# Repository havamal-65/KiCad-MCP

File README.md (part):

# KiCad MCP Server

A pure Python [Model Context Protocol (MCP)](https://modelcontextprotocol.io) server for KiCad EDA automation. Enable AI assistants like Claude, Cursor, and others to interact with KiCad projects programmatically.

## Overview

KiCad MCP Server provides a standardized interface for AI assistants to read, analyze, and modify KiCad electronic design automation (EDA) files. It supports multiple backend implementations to work with KiCad in different environments and use cases.

### Key Features

- **121 MCP Tools** across 11 categories:
  - 📋 **Project Management** (15 tools): Create projects, open projects, list files, read/write metadata, text variable management, query backend info, query active KiCad project (IPC-first, with bridge fallback), PCB workflow reference, plan capture and retrieval, **KiCad 9→10 project format upgrade** (kicad-cli-driven, backed up, one-way), **8-item startup gate checklist**
  - 📐 **Schematic Operations** (29 tools): Create schematics from scratch, place/remove/move components, wire routing, labels (add/remove/edit label text), no-connects, junctions, power symbols, bulk component / power-symbol / pin-net / no-connect / move operations (drop ~200 calls per design to ~10), property editing, **symbol attribute authoring and editing** (`in_bom` / `on_board` / `dnp` / `exclude_from_sim`), pin position queries (with `extends` resolution **and audited rotation/mirror math against eeschema**), net connectivity analysis, hierarchical sheet traversal, schematic-to-PCB comparison and sync (with **PlacementIntent** schematic-driven anchoring + sheet-path propagation)
  - 🔌 **PCB Board Operations** (21 tools): Read boards, place/move components, add tracks/vias/board outlines, assign nets, query design rules, **author/list/delete copper pour zones** plus refill, **silkscreen refdes tidying** (relocate-first, hide-fallback), query layer stackup, write IPC-2221/JLCPCB design rules, geometry-driven auto-placement (with **sheet-hierarchy clustering** and **anchors** parameter so place_at_edge work survives bulk placement), **board-size verification gate**, full schematic-to-routed-PCB pipeline (with mandatory pre-flight gate), **diff two board snapshots**, **anchor an edge-facing connector at a named board edge with correct outward rotation**
  - 📚 **Library Search** (8 tools): Search symbols/footprints, list libraries, get symbol/footprint info, suggest footprints for a symbol (with physical dimensions), query footprint courtyard dimensions, **estimate board size from footprint list**
  - 📦 **Library Management** (9 tools): Clone repos, register sources, import symbols/footprints, create project libraries
  - ✅ **Design Rule Checks** (13 tools): Run DRC and ERC validations, file-based schematic and board validation (no kicad-cli), kicad-cli strict schematic validation, query board design rules, **symbol/footprint pad-match validator**, **pre-sync schematic completeness check**, **fast courtyard overlap check**, **placement-quality gate** (keep-out intrusion + net-aware metric), **detect edge-facing connectors** (USB-C, JST, audio jacks, etc.), **validate connector orientations** with autoroute hash-gate that refuses to route over inward-facing connectors
  - 📤 **Export Operations** (9 tools): Export Gerbers, drill files, BOMs, pick-and-place, PDFs (with actionable error diagnostics), **3D STEP and VRML models** (STEP with a three-way success / partial / error verdict), **verify 3D model references resolve on disk**, **render a board or schematic to an image for visual self-inspection**
  - 🏭 **Manufacturing** (1 tool): One-call **manufacturing-readiness audit** — DRC + board-size + courtyard + 3D-model + all five fab artifacts with a structured ship/no-ship verdict
  - 🎛️ **Design Variants** (4 tools, KiCad 10+): Create/delete variants, set per-component overrides (DNP, BOM/position exclusion, field values — schematic and board sides in one call), list variants with cross-file consistency checks; all writes kicad-cli-validated and atomic, structured refusal on KiCad 9
  - 🔀 **Auto-Routing** (6 tools): PCB trace auto-routing — **TraceMaker preferred when its WSL runtime is detected, with automatic FreeRouting fallback** (both optional; `router` parameter forces either engine), **clean board for routing**, **clear all routes for re-placement**
  - 🔍 **Parts Catalog** (6 tools): Index and search third-party KiCad library sources by MPN, install parts into project libraries

- **Plugin Backend Architecture**: `PluginDirectBackend` routes each operation to the right subsystem — no fallback ambiguity:
  - **Board read/write** → KiCad IPC API (`kicad-python`/`kipy`) as the primary live path, TCP bridge to embedded `pcbnew` as fallback, then the file backend when KiCad is closed (writes safe-refuse rather than clobber a live board). Requires KiCad open for live ops.
  - **Schematic read/write** → Pure Python file backend (no KiCad instance required)
  - **DRC / export** → `kicad-cli` subprocess
  - **Library search/management** → Pure Python file backend
- **Safe Response Sizes**: Large list results (symbols, wires, tracks, components) are automatically capped to prevent AI token-limit errors. Truncated fields include `<field>_total` and `<field>_truncated` metadata so you always know the full count.
- **Change Tracking**: Built-in logging of all operations for debugging and auditing
- **Backup Support**: Automatic file backups before modifications
- **Flexible Configuration**: Environment variables, CLI args, or programmatic config

## Installation

### Requirements

- Python 3.10 or higher
- KiCad 7.0+ (optional, depending on backend)

### From PyPI (Coming Soon)

```bash
python -m venv .venv
source .venv/bin/activate   # Windows: .venv\Scripts\activate
pip install kicad-mcp
```

### From Source

```bash
git clone https://github.com/havamal-65/KiCad-MCP.git
cd KiCad-MCP
pip install -e .
```

### Optional Dependencies

Activate the venv first, then install the extras inside it:

```bash
source .venv/bin/activate   # Windows: .venv\Scripts\activate
```

For auto-routing functionality, install at least one routing engine (the `autoroute`
tool prefers TraceMaker when it is available and falls back to FreeRouting
automatically — see [Auto-Routing](#auto-routing-6-tools---optional)):

- **TraceMaker** (Windows, via WSL2): build [TraceMaker](https://github.com/DingoOz/TraceMaker)
  inside a WSL2 distro. By default the tool looks for distro `tracemaker-build` and
  binary `~/TraceMaker/build/cpu-only/src/app/tracemaker`; override with
  `KICAD_MCP_TRACEMAKER_DISTRO` and `KICAD_MCP_TRACEMAKER_BIN`. Set
  `KICAD_MCP_NO_TRACEMAKER=1` to disable detection entirely.
- **FreeRouting** (all platforms, requires Java):
  - Download [FreeRouting JAR](https://github.com/freerouting/freerouting/releases)
  - Ensure Java Runtime Environment (JRE) is installed
  - Set `KICAD_MCP_FREEROUTING_JAR` and `KICAD_MCP_JAVA_PATH` environment variables (or let the tool auto-detect)

For development:
```bash
pip install kicad-mcp[dev]
```

For the desktop launcher (a status dashboard that brings up the whole stack — see
[Desktop Launcher](#desktop-launcher-ui) below):
```bash
pip install kicad-mcp[launcher]   # pywebview + psutil
```
On Windows the launcher uses the system **WebView2** runtime (preinstalled on
Windows 11). It is a standalone dev tool run from source and is **not** part of the
MCP server install.

## Claude Code Skill: `/build-pcb`

When using this server with Claude Code, invoke `/build-pcb [project description]` to
start a **professional, phased PCB design session**. The skill mirrors IPC/JEDEC
industry practice with seven gated phases and a report + user confirmation between each:

| Phase | Name | Gate condition |
|-------|------|---------------|
| 1 | Environment & Requirements | `get_startup_checklist.ready_for_pcb` |
| 2 | Schematic Capture | All components placed, ≥1 net |
| 3 | Schematic Verification | `validate_schematic_for_pcb.ready_for_pcb_sync`, ERC clean |
| 4a | Sync & Survey | every ref from `identify_edge_facing_connectors` has a planned edge |
| 4b | Anchor Connectors | `validate_connector_orientations.passed` after `place_at_edge` for each |
| 4c | Bulk Placement | every non-anchored ref placed; anchors passed via `auto_place(anchors=[...])` |
| 4d | Overlap Check | `check_courtyard_overlaps.passed` |
| 4e | Final Orientation Re-check | `validate_connector_orientations.passed` (autoroute refuses if not) |
| 5 | Routing | Zero unrouted connections |
| 6 | Design Verification | `run_drc.passed` |
| 7 | Manufacturing Outputs | All six export files generated |

After each phase Claude prints a `## Phase N Report` block and pauses for your
confirmation before continuing. Hard gates prevent routing over courtyard overlaps,
routing past inward-facing connectors, or syncing a schematic with blocking issues.

---

## Quick Start

### Plugin Entry Point (recommended on Windows with KiCad 9)

The plugin entry point routes board operations through the in-KiCad TCP bridge (`kicad_mcp_bridge`) and is the primary supported path for live PCB work.

**Prerequisites**: Install the bridge plugin and restart KiCad (see [Plugin Backend Setup](#plugin-backend-setup) below).

```bash
python -m kicad_mcp_plugin
```

### Run the Server

#### Stdio Transport (for Claude Desktop, Cursor, etc.)

```bash
python -m kicad_mcp_plugin
```

#### SSE Transport (for web clients)

```bash
python -m kicad_mcp_plugin --transport sse --sse-host 127.0.0.1 --sse-port 8765
```

## Desktop Launcher (UI)

A standalone desktop app that brings up and monitors the whole KiCad ↔ MCP stack
from one window — so you don't have to start pcbnew, the MCP server, and Claude Code
by hand. It's a **status-first dashboard** that shows, live, whether an AI agent can
currently reach and edit a board.

**What it shows** (all real, polled from the same health collectors the MCP uses —
no mock data):

- **pcbnew bridge** and **MCP server** status tiles (connected / running / pid / uptime)
- the **`ready_for_pcb` gate** — a live `n/6` progress bar over the six startup checks
- the four **backends** (`plugin`, `file`, `cli`, `subprocess`) and their availability
- **tool-activity** and **server.log** feeds (only real events — quiet when idle)
- an **actionable guidance** callout that turns a passive status into the next step
  (server stopped → *Start everything*; bridge down → *Open PCB editor*; checks
  incomplete → *Reload board*)

**Actions**: a project picker plus **Start everything** (opens pcbnew on the selected
board, starts the MCP HTTP server, and launches a Claude Code session), **Restart MCP**
(reloads server code without the manual kill + `/mcp`), and **Stop MCP**.

**Run it** (after `pip install kicad-mcp[launcher]`):

```bash
python -m launcher
```

On Windows you can also double-click / run `launcher/launcher.ps1` for a windowless
(`pythonw`) launch. The launcher never modifies the MCP server or the bridge; it
reuses `scripts/mcp_health_monitor.py`'s collectors for status and drives the same
tools you'd call by hand. Configure it with the same environment variables as the
server (e.g. `KICAD_MCP_HTTP_HOST`/`KICAD_MCP_HTTP_PORT`, `KICAD_MCP_PROJECTS_ROOT`).

### Packaged app (no Python required)

A double-click Windows installer bundles the launcher, the MCP server, and a
Python runtime — nothing to `pip install`, no terminal:

1. Build (or download) `KiCad-MCP-Launcher-Setup-<version>.exe` — built from a
   checkout with one command: `pwsh -File installer\build.ps1`.
2. Run it. **The installer is unsigned**, so Windows SmartScreen will warn:
   click **More info → Run anyway**. (Unsigned-with-docs is the deliberate
   ship decision; the build script signs everything automatically if you
   supply a code-signing certificate: `installer\build.ps1 -CertPath ...`.)
3. It installs per-user (no admin prompt) to
   `%LOCALAPPDATA%\Programs\KiCad-MCP Launcher`, adds a Start-Menu shortcut,
   and opens the launcher. On first run the **Setup view** walks the
   remaining pieces: detect KiCad, install the bridge, register the MCP with
   Claude Code — all from the window.
4. KiCad itself stays a prerequisite (the wizard links to its download);
   uninstalling removes the app but deliberately leaves the bridge and your
   MCP client config in place (they belong to your KiCad/client setup).

The `pip install` dev path above keeps working unchanged; the packaged app is
additive. Requires the Microsoft WebView2 runtime (preinstalled on Windows 11;
the app shows the official download link if it's missing).

## Configuration

### Environment Variables

```bash
# Transport: stdio, sse, streamable-http
KICAD_MCP_TRANSPORT=stdio

# Logging level: DEBUG, INFO, WARNING, ERROR
KICAD_MCP_LOG_LEVEL=INFO

# Log file path (default: ~/.kicad-mcp/logs/server.log)
KICAD_MCP_LOG_FILE=

# Explicit path to kicad-cli executable
KICAD_MCP_KICAD_CLI_PATH=

# Enable file backups before modification (default: true)
KICAD_MCP_BACKUP_ENABLED=true

# Bridge port (default: 9760)
KICAD_MCP_PLUGIN_PORT=9760

# Network bind (only used with --transport sse / streamable-http)
KICAD_MCP_SSE_HOST=127.0.0.1
KICAD_MCP_SSE_PORT=8765
```

### Programmatic Configuration

```python
from kicad_mcp_plugin.config import KiCadPluginConfig
from kicad_mcp_plugin.server import create_plugin_server

config = KiCadPluginConfig(log_level="INFO")
mcp = create_plugin_server(config)
mcp.run(transport="stdio")
```

## Client Integration

The repo ships bootstrap scripts for the plugin entry point:

- **`run_plugin.ps1`** — Windows (PowerShell 7+)
- **`run_plugin.sh`** — macOS / Linux

These automatically create a virtual environment and install all dependencies on first run, and they clear inherited `PYTHONHOME` / `PYTHONPATH` overrides so MCP clients use the repo's venv instead of global Python packages.

### Codex CLI

Register the server once with `codex mcp add`:

Windows:

```powershell
codex mcp add kicad `
  --env KICAD_MCP_LOG_LEVEL=INFO `
  -- "C:\Windows\System32\WindowsPowerShell\v1.0\powershell.exe" `
  -ExecutionPolicy Bypass `
  -NonInteractive `
  -File "C:\path\to\KiCad-MCP\run_plugin.ps1"
```

macOS / Linux:

```bash
codex mcp add kicad \
  --env KICAD_MCP_LOG_LEVEL=INFO \
  -- /path/to/KiCad-MCP/run_plugin.sh
```

Verify with:

```bash
codex mcp get kicad
```

### Claude Code (recommended)

A `.mcp.json` is included at the repo root. Claude Code picks it up automatically when you open the folder, so no manual config is required. It uses the plugin entry point (`kicad_mcp_plugin`) by default, which requires KiCad to be open with the bridge installed.

### Claude Desktop — Windows

Add to `%APPDATA%\Claude\claude_desktop_config.json`:
Use an absolute PowerShell path to avoid `Executable not found in $PATH: "powershell"` startup errors.

```json
{
  "mcpServers": {
    "kicad": {
      "command": "C:\\Windows\\System32\\WindowsPowerShell\\v1.0\\powershell.exe",
      "args": [
        "-ExecutionPolicy", "Bypass",
        "-NonInteractive",
        "-File", "C:\\path\\to\\KiCad-MCP\\run_plugin.ps1"
      ],
      "env": {
        "KICAD_MCP_LOG_LEVEL": "INFO"
      }
    }
  }
}
```

### Claude Desktop — macOS / Linux

Add to `~/Library/Application Support/Claude/claude_desktop_config.json` (macOS) or `~/.config/Claude/claude_desktop_config.json` (Linux):

```json
{
  "mcpServers": {
    "kicad": {
      "command": "/path/to/KiCad-MCP/run_plugin.sh",
      "env": {
        "KICAD_MCP_LOG_LEVEL": "INFO"
      }
    }
  }
}
```

### Cursor

Add to your Cursor MCP settings (use `run_plugin.ps1` on Windows, `run_plugin.sh` on macOS/Linux as above).

### Manual setup (advanced)

If you prefer to manage your own venv:

```bash
python -m venv .venv
source .venv/bin/activate   # Windows: .venv\Scripts\activate
pip install -e .
python -m kicad_mcp_plugin
```

## Available Tools

### Project Management (15 tools)
- `open_kicad`: Launch KiCad and wait for the bridge to become ready
- `open_project`: Open a KiCad project and return its structure
- `list_project_files`: List all KiCad-related files in a project directory
- `get_project_metadata`: Read detailed metadata from a KiCad project file
- `save_project`: Trigger save for an open KiCad project (requires bridge)
- `get_backend_info`: Get information about available backends and their capabilities
- `get_active_project`: Query the currently open KiCad project and board path (requires bridge)
- `get_text_variables`: Get all project-level text variables (`${VAR}` substitutions)
- `set_text_variables`: Set one or more project-level text variables
- `create_project`: Create a new KiCad project with blank `.kicad_pro`, `.kicad_sch`, and `.kicad_pcb` files
- `get_pcb_workflow`: Return a structured 11-step PCB design workflow reference (JSON) showing the recommended tool sequence from project creation through DRC
- `plan_project`: Record a structured project plan into a `project_plan.json` file. When `board_width_mm`/`board_height_mm` are 0 (default) and footprint IDs are included in `key_components`, auto-estimates board dimensions from courtyard bounds. Emits a `size_warning` when provided dimensions are more than 15% smaller than the estimate.
- `read_project_plan`: Read back the saved project plan for a given project directory
- `upgrade_project_format`: Upgrade a project's schematic and board files from KiCad-9 to KiCad-10 format via KiCad's own `kicad-cli sch/pcb upgrade`, backing up every changed file first. One-way (KiCad 9 cannot re-open v10 files; the `.kicad_mcp_backups/` copies are the rollback); refuses without touching any file if no KiCad-10 kicad-cli is available. Needed before the Design Variants tools on a v9-format project
- `get_startup_checklist`: Run an eight-item PASS/WARN/FAIL gate before any board operation: KiCad running (counts pcbnew/eeschema too) · IPC API server reachable · bridge reachable · bridge version · PCB editor open (board-ready aware — distinguishes "still loading" from "no board") · live board ↔ file coherence (WARNs with a reload advisory when the open board's component set or Edge.Cuts outline diverges from the file on disk) · kicad-cli on PATH · active project loaded. A down bridge is a non-blocking WARN whenever the IPC path already serves the open board (and vice-versa). Returns `ready_for_pcb` bool and `required_actions` list. **Must be called at the start of every session involving PCB operations.**

### Schematic Operations (29 tools)
- `read_schematic`: Read complete schematic structure (symbols, wires, labels, no-connects, junctions). Every symbol row carries the four attribute flags (`in_bom`, `on_board`, `dnp`, `exclude_from_sim`)
- `create_schematic`: Create a new, empty KiCad 8+ schematic file with proper structure
- `add_component`: Place symbols with rotation, mirror, footprint, custom properties, KiCad 8+ instance data, and optional symbol attribute flags (`in_bom`, `on_board`, `dnp`, `exclude_from_sim` — e.g. keep a mounting hole out of the BOM at placement time)
- `add_components`: **Bulk** — place N components in one call (single file read/write). Prefer over looping `add_component`.
- `add_wire`: Draw wire connections between two points
- `add_label`: Add net labels (net, global, hierarchical)
- `remove_label`: Remove a net label by its position
- `set_label_text`: Change the text of an existing net label
- `add_no_connect`: Add no-connect (X) markers to unused pins
- `add_no_connects`: **Bulk** — mark N unused pins in one call.
- `add_power_symbol`: Add power symbols (+3V3, GND, VCC, etc.) with auto-incrementing references
- `add_power_symbols`: **Bulk** — place N power symbols in one call; #PWR refs auto-incremented across the batch.
- `connect_pins`: **Bulk** — net N pins together with one call by emitting stub-and-label connectivity. Replaces the `add_wire + add_label` × N pattern (~6 calls per net) with one call.
- `add_junction`: Add junction dots at wire intersections
- `remove_component`: Remove a placed component by reference designator
- `remove_wire`: Remove a wire segment by its endpoint coordinates
- `remove_no_connect`: Remove a no-connect marker by its position
- `move_schematic_component`: Move a component to a new position with optional rotation (shifts property labels too)
- `move_components`: **Bulk** — reposition N components in one call (single file read/write).
- `update_component_property`: Update or add a property (Value, Footprint, MPN, etc.) on a placed component
- `set_symbol_attributes`: Edit the four attribute flags (`in_bom`, `on_board`, `dnp`, `exclude_from_sim`) on an already-placed symbol — only the flags you pass change; multi-unit symbols are updated across every unit and the per-unit results reported
- `get_symbol_pin_positions`: Get absolute schematic coordinates for each pin of a placed symbol; resolves `extends` chains so symbols like ATtiny85-20S and AMS1117-3.3 work correctly, and applies KiCad's rotation/mirror transform (audited against eeschema's own placement so rotated/mirrored symbols resolve correctly)
- `get_pin_net`: Get the net name connected to a specific pin of a symbol
- `get_net_connections`: Get all connections (pins, labels, wires) on a named net
- `get_sheet_hierarchy`: Get the hierarchical sheet tree from a root schematic
- `compare_schematic_pcb`: Detect mismatches between schematic and PCB (missing components, footprint/value differences)
- `sync_schematic_to_pcb`: Synchronize schematic components to the PCB (auto-place missing, update values, sync pin nets to pad net assignments). Reads each symbol's `PlacementIntent` custom property: `edge:north|south|east|west` anchors the corresponding footprint at that edge with correct outward rotation (skipped with a warning if no Edge.Cuts outline yet); `cluster:NAME` attaches a `ClusterId` to the footprint so `auto_place` keeps that subsystem geometrically grouped. Sheet hierarchy from `.kicad_sch` is propagated to placed footprints as a `(path "/UUID/...")` clause so `auto_place` clusters by schematic block automatically.
- `annotate_schematic`: Auto-annotate component reference designators
- `generate_netlist`: Generate netlist from schematic

### PCB Board Operations (21 tools)
- `read_board`: Read complete board structure
- `get_board_info`: Get board metadata (title, revision, layers, counts)
- `place_component`: Place a component footprint on the board
- `move_component`: Move an existing component to a new position
- `place_at_edge`: Anchor an edge-facing connector at the named board edge (`north` / `south` / `east` / `west`) with the correct outward rotation and a configurable courtyard-clearance offset. Reads the connector's local-frame mating face (via the same detection `validate_connector_orientations` uses) and computes the rotation that makes it point outward. Use in `/build-pcb` Phase 4b before `auto_place(anchors=[...])`.
- `add_track`: Add a copper track segment
- `add_via`: Add a via (through-hole, blind, or buried)
- `add_board_outline`: Add or replace the Edge.Cuts board outline with a rectangle at the specified origin and size. When called via `pcb_pipeline`, the board is automatically centered at the KiCad canvas origin (0, 0) so it always appears in the middle of the work area.
- `assign_net`: Assign a net to a component pad
- `get_design_rules`: Get the board's design rules (clearances, track widths, via sizes)
- `refill_zones`: Refill all copper pour zones on a board
- `add_zone`: Add a copper pour zone (e.g. a GND plane) from an explicit polygon or, with `follow_board_outline`, a rectangle derived from the Edge.Cuts bounding box inset by a margin. The zone is filled via a kicad-cli subprocess so the saved file carries real fill geometry
- `list_zones`: List every zone on a board, including rule (keep-out) areas — reads the saved `.kicad_pcb` directly so the answer is always file truth
- `delete_zone`: Delete one copper zone by name or uuid (rule areas are refused — use the keep-out tools for those)
- `tidy_silkscreen`: Reduce silkscreen DRC warnings by tidying reference-designator text — relocate each clipped/overlapping refdes to the nearest clear spot first, hide only small passives with nowhere clear to go (IC and connector refs are never hidden), then re-run DRC and report the delta
- `get_stackup`: Get the layer stackup definition for a board
- `verify_board_size`: Gate that asserts the chosen board size accommodates the placed parts plus manufacturing tolerances (panelization keepout, mounting holes, fiducials, routing channels). Returns `{passed, total_required_mm2, available_mm2, shortfall_breakdown, suggested_min_dimensions}` and is a precondition on `auto_place`.
- `set_board_design_rules`: Write manufacturing-enforceable design rules into the `.kicad_pro` `net_settings.classes` Default entry. Preset `"class2"` applies IPC-2221 Class 2 / IPC-7351 Level B values (0.20 mm clearance, 0.25 mm trace, 0.30 mm via drill). Preset `"fab_jlcpcb"` applies JLCPCB 2-layer standard rules.
- `auto_place`: Geometry-driven bin-packing placement. Reads the courtyard extents for every footprint, sorts by component class (connectors → ICs → discretes → transistors → LEDs → others), and packs components into rows with a guaranteed courtyard-to-courtyard gap ≥ `clearance_mm`. Returns `utilization_pct` (courtyard area / board area) and warns when >70%. Accepts an optional `anchors=[ref,...]` list — those refs are skipped so `place_at_edge`'s work survives bulk placement. Groups components by schematic sheet path (or explicit `PlacementIntent: cluster:NAME`) so circuit blocks land near each other.
- `diff_board`: Detect changes between two PCB board snapshots. Compares component positions and track counts between two `.kicad_pcb` files. Returns `added_components`, `removed_components`, `moved_components`, and `track_delta`. Useful for confirming `autoroute` added tracks or `auto_place` moved all components.
- `pcb_pipeline`: Full schematic-to-routed-PCB pipeline in a single call. Step 0 runs a mandatory pre-flight gate (startup checklist + `validate_schematic_for_pcb` + board-size estimate); Steps 1–6: `sync_schematic_to_pcb` → `set_board_design_rules` → add Edge.Cuts outline (centered at origin) → `auto_place` → **courtyard overlap check** (fails pipeline if overlaps present) → **connector orientation check** (fails if any edge-facing connector points inward) → `autoroute` → `run_drc`. Pipeline aborts with a clear error if any gate fails.

### Library Search (8 tools)
- `search_symbols`: Search for schematic symbols across installed libraries
- `search_footprints`: Search for PCB footprints across installed libraries
- `list_libraries`: List all available symbol and footprint libraries
- `get_symbol_info`: Get detailed information about a specific symbol
- `get_footprint_info`: Get detailed information about a specific footprint
- `suggest_footprints`: Suggest matching footprints for a symbol based on its footprint filters (searches all installed footprint libraries). Each result includes `width_mm`, `height_mm`, and `area_mm2` so you can make size-aware selections.
- `get_footprint_bounds`: Get the courtyard bounding box (`xmin`, `ymin`, `xmax`, `ymax`), `width_mm`, `height_mm`, and pad list for any footprint before placing it. Use this to compute non-overlapping placement positions.
- `estimate_board_size`: Calculate minimum board dimensions from a list of footprint IDs before calling `plan_project`. Sums courtyard areas, adds routing overhead (default 20%), edge clearance (default 3 mm per side), rounds to the nearest 5 mm fab grid, and applies a final dimensional margin (default 25%). Returns `recommended_width_mm`, `recommended_height_mm`, and a per-component breakdown. **Call this before `plan_project` — never guess board size.**

### Library Management (9 tools)
- `clone_library_repo`: Clone a remote KiCad library repository
- `register_library_source`: Register a local directory as a searchable library source
- `list_library_sources`: List all registered external library sources
- `unregister_library_source`: Remove a library source registration
- `search_library_sources`: Search for symbols/footprints across registered external sources
- `create_project_library`: Create an empty project-local KiCad library
- `import_symbol`: Copy a symbol from one .kicad_sym library to another
- `import_footprint`: Copy a footprint from one .pretty directory to another
- `register_project_library`: Register a library in a project's sym-lib-table or fp-lib-table

### Design Rule Checks (13 tools)
- `run_drc`: Run Design Rule Check on a PCB board
- `run_erc`: Run Electrical Rules Check on a schematic
- `validate_symbol_footprint_pairs`: Verify every symbol's `Footprint` field resolves to a real `.kicad_mod` with matching pad numbering and count. A hard precondition on `sync_schematic_to_pcb` — blocks sync when a pad-count/numbering mismatch would produce unassigned pads.
- `placement_quality`: Report placement-quality metrics for a board (net-aware HPWL metric, decap proximity, keep-out intrusion) without gating.
- `validate_placement_quality`: Blocking placement-quality gate — fails on `keepout_intrusion` (a footprint courtyard inside a keep-out zone) and reports the net-aware `placement_metric`. `autoroute` refuses to run when this most-recent check is missing or failed for the current board hash.
- `validate_schematic`: File-based electrical rules validation (no kicad-cli required)
- `validate_schematic_cli`: Validate schematic loadability using kicad-cli's strict C++ symbol loader. Exercises symbol geometry and `extends` chain resolution that the Python API accepts but kicad-cli export may reject. Returns `{"passed": bool, "backend": "kicad-cli", "message": "..."}` or `{"status": "unavailable"}` when kicad-cli is not installed.
- `validate_board`: File-based pre-flight checks for a PCB board (no kicad-cli required). Checks: Edge.Cuts outline present (error), duplicate reference designators (error), footprints at (0, 0) (warning), design rules block absent (warning). Returns `{"passed": bool, "violations": [...], "error_count": n, "warning_count": n}`.
- `get_board_design_rules`: Get the design rules configured for a board
- `validate_schematic_for_pcb`: Pre-sync completeness check (no kicad-cli required). Verifies every component has a Footprint, references are unique, PWR_FLAG symbols cover power nets, no component sits at (0, 0), net count is non-zero, and optionally runs full ERC if kicad-cli is available. Returns `ready_for_pcb_sync` bool and a `blocking_issues` list. **Must pass before calling `sync_schematic_to_pcb`.**
- `check_courtyard_overlaps`: Fast file-based courtyard AABB intersection check (milliseconds, no kicad-cli). Returns `passed` bool and a list of overlapping component pairs with `overlap_x_mm`, `overlap_y_mm`, and `suggested_move_mm`. **Must pass before calling `autoroute`.**
- `identify_edge_facing_connectors`: Detect connectors that need outward-facing placement at a board edge (USB-C, JST PH/XH, audio jacks, barrel jacks, RJ45, HDMI, etc.). Uses three signals, highest confidence first: KiCad library's `Dwgs.User` "PCB edge" marker, F.SilkS centroid asymmetry, and footprint-name heuristics. Returns each ref's `mating_face` in footprint-local frame plus `confidence` and `evidence`. A name match whose only token hit is the generic orientation word "Horizontal" is kept only when the refdes class is a connector class (J/P/X/XP/XS/CON) — axial passives are silently skipped. Use this as Phase 4a's survey step in `/build-pcb`.
- `validate_connector_orientations`: Placement-quality gate for edge-facing connectors. For each ref from `identify_edge_facing_connectors`, applies the placed rotation to the mating-face vector, checks it points toward the closest board edge within ±30°, and accepts any of multiple equidistant edges within 2 mm (corner-placement tolerance). Returns `passed` bool, `violations` (with `suggested_edge` and `suggested_rotation`), and `indeterminate` (refs needing manual review). **Side effect**: writes the result to `<board>.validation_cache.json` so `autoroute` can refuse to run when this most-recent check is missing or failed for the current board hash. **Must pass before calling `autoroute`.**

### Export Operations (9 tools)
- `export_gerbers`: Export Gerber manufacturing files from a PCB board
- `export_drill`: Export drill files (Excellon format)
- `export_bom`: Export Bill of Materials (CSV, JSON, etc.)
- `export_pick_and_place`: Export pick-and-place component placement file
- `export_pdf`: Export a board or schematic to PDF. Verifies kicad-cli is on PATH before attempting export and confirms the output file was actually created. On failure, surfaces the exact kicad-cli command attempted and stderr so you can diagnose the root cause.
- `export_step`: Export a 3D STEP model from a PCB board for mechanical integration. Requires kicad-cli. Status is three-way: `success` (clean export), `partial` (kicad-cli exited nonzero but wrote a structurally valid STEP this run — e.g. VRML-only 3D models it cannot convert; the payload lists the excluded models and a remedy), or `error` (no usable file). A bare nonzero exit is never misreported as success.
- `render_view`: Render a board or schematic to an image for visual inspection — boards to PNG via `kicad-cli pcb render` (3D view, top side by default), schematics to PDF. Built so an AI agent can actually look at what it built; board renders save the live board state to disk first so the image matches reality.
- `export_vrml`: Export a 3D VRML model from a PCB board for 3D rendering and simulation tools. Requires kicad-cli.
- `verify_3d_models`: Walk every footprint's `(model …)` clause, expand KiCad path variables (`${KICAD9_3DMODEL_DIR}`, etc.), and check each referenced 3D model resolves on disk (with a `.wrl`↔`.step` sibling fallback) before `export_step` fails at render time. Distinguishes `file_not_found` from `unresolved_variable`.

### Manufacturing (1 tool)
- `manufacturing_readiness_audit`: One call returns a structured ship/no-ship verdict covering DRC, board-size verification, courtyard overlaps, 3D-model resolution, and all five fab artifacts (Gerbers, drill, BOM, pick-and-place, STEP). Returns `{ready_to_ship, checks: [{name, passed, detail, artifact_path}], blocking_issues}`. A partial STEP export (valid file despite excluded 3D models) surfaces as a non-blocking `partial_step` advisory naming the excluded models — the audit can still be `ready_to_ship`. Projects with design variants (KiCad 10+) run the audit once per shipping variant via `variant="<name>"` — artifacts land under `<output_dir>/<variant>/`. `/build-pcb` Phase 7 uses this instead of running each export individually.

### Design Variants (4 tools, KiCad 10+)
Author design variants (e.g. a "no-debug-header" assembly) at design stage; every write is validated with kicad-cli before the originals are replaced (a failed validation leaves every file byte-identical), and the tools refuse with a structured payload on KiCad 9.

- `create_variant`: Register a variant in the `.kicad_pro` and (when a board exists) the `.kicad_pcb` board registry — both sides in one operation
- `set_variant_overrides`: Set per-variant overrides on one component, schematic symbol AND board footprint in one call (DNP, BOM/position-file exclusion, field values; positive logic — `in_bom=False` means excluded) so variant BOM/pos/gerber exports stay coherent
- `list_variants`: Read-only merge of all three files (project registry, schematic overrides, board overrides) with cross-file inconsistency flags — works on any KiCad version
- `delete_variant`: Remove a variant fully — registry entries and every per-component override block on both sides, no orphan tokens

### Auto-Routing (6 tools) - Optional
**Requires:** at least one routing engine — [TraceMaker](https://github.com/DingoOz/TraceMaker) (Windows, running inside WSL2) and/or [FreeRouting](https://github.com/freerouting/freerouting) with Java

These tools provide automated PCB trace routing capabilities:
- `export_dsn`: Export PCB to Specctra DSN format for FreeRouting
- `import_ses`: Import routed SES session file back into PCB
- `run_freerouter`: Execute FreeRouting auto-router on a DSN file
- `clean_board_for_routing`: Remove keepouts and problematic tracks before routing
- `autoroute`: Complete routing pipeline with engine selection via the `router` parameter (`"auto"` default / `"tracemaker"` / `"freerouting"`). In `auto` mode the tool prefers TraceMaker when its WSL runtime is detected (routes the `.kicad_pcb` directly, imports the new tracks through the live bridge when one is up), and **any TraceMaker failure falls back to the full FreeRouting pipeline (clean → DSN export → route → SES import) in the same call**. TraceMaker detection honors `KICAD_MCP_TRACEMAKER_DISTRO` / `KICAD_MCP_TRACEMAKER_BIN` and the `KICAD_MCP_NO_TRACEMAKER=1` kill-switch. Run post-route DRC as the completion oracle
- `clear_routes`: Remove all routed tracks and vias from a board, preserving footprint placement, nets, and the board outline. When the plugin bridge is active, mutates pcbnew's live in-memory board so the file and bridge cache stay in sync — subsequent `autoroute` calls see the cleared state and tracks do not compound across iterations. Falls back to direct file editing when the bridge is unreachable. Writes a `.clear_routes_backup.kicad_pcb` file before modifying.

> **Note**: The auto-routing tools are completely optional. All other KiCad-MCP functionality works without TraceMaker, FreeRouting, or Java.

### Parts Catalog (6 tools)
These tools index and search third-party KiCad library sources (GitHub releases, local directories) and install parts by MPN into project libraries. They extend the built-in Library Management tools with a content-addressed parts index.

- `list_known_sources`: List all well-known third-party KiCad library sources (name, URL, type, description)
- `bootstrap_known_source`: Download and register a well-known source by name (clones repo or extracts archive into `~/.kicad-mcp/sources/<name>/`, then registers it)
- `index_library_source`: Build or rebuild the parts index for a registered source (scans `.kicad_sym` / `.kicad_mod` files, extracts MPN and manufacturer fields)
- `search_parts`: Search the parts index by MPN, value, description, or manufacturer across all indexed sources. Returns ranked matches with symbol and footprint paths.
- `install_part`: Copy a part from an indexed source into a project-local library by MPN. Installs both symbol and footprint if available.
- `parts_index_stats`: Report index statistics for all registered sources (symbol count, footprint count, last indexed time, source path)

## Backend Details

### Plugin Entry Point Backend Routing

`kicad_mcp_plugin` (the recommended entry point on Windows) uses `PluginDirectBackend` with a defined routing order — the primary live path first, then explicit fallbacks:

| Operation | Backend |
|-----------|---------|
| Board read/write (place, move, track, via, zones, outline, DSN/SES) | KiCad IPC API (`kipy`) → plugin bridge (TCP → `pcbnew`) → file backend (KiCad closed only; writes safe-refuse rather than clobber a live board) |
| Schematic read/write | File backend |
| DRC / export (Gerbers, drill, BOM, PDF, STEP, VRML) | kicad-cli |
| Library search / management | File backend |

### Capability Routing (PluginDirectBackend)

| Operation | Subsystem | KiCad required? |
|-----------|-----------|-----------------|
| Board read/write | IPC API (`kipy`) → TCP bridge → pcbnew | Yes (PCB editor open) |
| Schematic read/write | File backend | No |
| DRC / ERC / export | kicad-cli | Yes (kicad-cli on PATH) |
| Library search/manage | File backend | No |
| Parts catalog | SQLite + HTTP APIs | No |

## Development

### Setup Development Environment

```bash
git clone https://github.com/havamal-65/KiCad-MCP.git
cd KiCad-MCP
pip install -e .[dev]
```

### Run Tests

Unit tests (no KiCad installation required — mocks `_tcp_call`, `is_kicad_running`, and footprint loaders):

```bash
pytest --tb=short -q
```

The suite covers tool logic, file backend behavior, bridge dispatch (mocked), and routing helpers. End-to-end behavior against a live `pcbnew` (e.g. confirming that `clear_routes` empties the bridge's in-memory cache) is exercised manually against the example projects in `examples/` rather than as automated CI.

### Code Quality

```bash
# Format and lint
ruff check .
ruff format .

# Type checking
mypy src
```

### Hot-reload dev server (no manual `/mcp`)

The committed `.mcp.json` uses **stdio**, which Claude Code spawns and owns — so
editing server code normally means killing the process and running `/mcp`. To
iterate without that, run the server over **streamable-http** under a
file-watcher and point Claude Code at the URL. Claude Code auto-reconnects to an
HTTP/SSE server when it restarts (exponential backoff), so a save just works.

```bash
# 1. one terminal: watch src/ and auto-restart the server on save
scripts/dev_server.sh          # or:  pwsh -File scripts/dev_server.ps1
#    → serves http://127.0.0.1:8765/mcp, restarts on any src/ change

# 2. launch Claude scoped to the dev (http) config instead of stdio
claude --strict-mcp-config --mcp-config .mcp.dev.json
```

Now edit a tool, save, and the next tool call uses the new code — no `/mcp`, no
process kill. End users are unaffected (the default `.mcp.json` stays stdio).
Bridge edits (`kicad_plugin/kicad_mcp_bridge.py`) are separate — see
"After Any Bridge Change" in `src/CLAUDE.md`.

### Project Structure

```
KiCad-MCP/
├── src/kicad_mcp/
│   ├── backends/          # plugin_backend, cli_backend, file_backend, subprocess_backend (helpers)
│   ├── models/            # Data models and error types
│   ├── resources/         # MCP resources
│   ├── tools/             # MCP tools (board, schematic, export, routing, library, DRC, project, parts)
│   └── utils/             # Utilities (platform detection, sexp parser, validation, parts index)
├── src/kicad_mcp_plugin/
│   ├── backends/
│   │   └── plugin_direct.py  # PluginDirectBackend — explicit routing, no fallbacks
│   ├── config.py          # Plugin entry point config (KICAD_PLUGIN_ env prefix)
│   ├── server.py          # MCP server — registers all 110 tools
│   └── __main__.py        # CLI entry point: python -m kicad_mcp_plugin
├── kicad_plugin/
│   ├── kicad_mcp_bridge.py  # KiCad ActionPlugin — TCP bridge (installed into KiCad)
│   └── install_bridge.ps1   # PowerShell installer (Windows, PowerShell 7+)
├── launcher/               # Desktop launcher (pywebview dashboard — see Desktop Launcher)
│   ├── app.py              #   webview host + LauncherApi (start/stop/restart, status)
│   ├── dashboard.py        #   pure collect()-snapshot → UI state mapping
│   ├── processes.py        #   pcbnew / MCP-server / Claude process control
│   ├── recents.py, config.py, orchestrator.py  # picker, config, bring-up logic
│   └── ui/index.html       #   the dark status-first dashboard (HTML/CSS/JS)
├── scripts/
│   └── mcp_health_monitor.py  # health collectors (reused by the launcher for status)
├── tests/                 # pytest suite (mocked _tcp_call — no live KiCad needed)
├── examples/              # Local-only worked builds (gitignored — see Examples section)
├── run_plugin.ps1         # Windows launcher for kicad_mcp_plugin (auto-creates venv)
├── run_plugin.sh          # macOS/Linux launcher for kicad_mcp_plugin
├── pyproject.toml         # Project metadata
└── README.md
```

## Use Cases

- **AI-Assisted PCB Design**: Let AI assistants help design and review circuits
- **Automated Quality Checks**: Run DRC/ERC as part of CI/CD pipelines
- **Batch Processing**: Automate repetitive design tasks across multiple projects
- **Design Analysis**: Extract and analyze design data programmatically
- **Documentation Generation**: Auto-generate BOMs, netlists, and design docs
- **Design Migration**: Convert or update designs programmatically

## Examples

The `examples/` directory is **gitignored** — it's a workspace for locally-built test boards rather than canonical reference designs that ship with the repo. Builds are produced by running `/build-pcb [description]` (or by calling the MCP tools directly) against a fresh project directory under `examples/`.

A typical build leaves behind:

- `<project>.kicad_pro`, `<project>.kicad_sch`, `<project>.kicad_pcb`
- `output/` containing exported gerbers, drill files, BOM, pick-and-place, and PDFs
- `output/known_issues.md` — any DRC exceptions, dangling tracks, or silk overlaps that were reviewed and accepted before fab

To reproduce an end-to-end build yourself:

```bash
# In Claude Code with KiCad open and the bridge installed
/build-pcb air quality sensor with BME680 and ESP32-C3
```

The skill enforces the seven-phase workflow described above (Environment & Requirements → Schematic Capture → Verification → Setup & Placement → Routing → DRC → Manufacturing Outputs) and pauses for confirmation between phases.

## Troubleshooting

### Does KiCad-MCP require FreeRouting or TraceMaker?

**No.** Routing engines are completely optional and only needed if you want to use the 6 auto-routing tools. All other 115 tools work without TraceMaker, FreeRouting, or Java.

When you do route, `autoroute` prefers TraceMaker if its WSL runtime is detected and falls back to FreeRouting automatically; either engine alone is enough. If neither is installed, you'll get a helpful error message with setup instructions.

### Plugin Backend Setup

The plugin backend gives the MCP direct live access to `pcbnew`'s in-memory board data while KiCad is open, with no gRPC overhead. It works on **Windows, Linux, and macOS** with KiCad 9.

The install scripts:
1. Remove any stale bridge copies from `scripting/plugins/` (these cause a `sys.modules` conflict that silently prevents the bridge from starting)
2. Install `kicad_mcp_bridge.py` as `__init__.py` in KiCad's PCM plugins directory
3. Patch `pcbnew.json` so KiCad auto-loads the bridge on every pcbnew startup

**Windows (PowerShell 7+):**

```powershell
pwsh -ExecutionPolicy Bypass -File kicad_plugin\install_bridge.ps1
```

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
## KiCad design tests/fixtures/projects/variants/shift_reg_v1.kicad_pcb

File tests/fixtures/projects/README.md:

# Project fixtures

## `diffpair_ground_truth.kicad_pro` / `diffpair_ground_truth.kicad_dru`

**Provenance:** verbatim copies of KiCad 9's shipped demo project
`vme-wren` (`<KiCad>/share/kicad/demos/vme-wren/vme-wren.{kicad_pro,kicad_dru}`),
renamed only. Unmodified content — these are *captured* real-KiCad-authored
files, the ground truth for the §6.4 differential-pair format (REQ-FMT-001).

**License:** KiCad demo projects are distributed with KiCad under
GPL-3.0-or-later. Retained here unmodified for test purposes with attribution.

**What they pin (the writer must reproduce these structures):**

- **Diff-pair fields on a netclass** — each `net_settings.classes[i]` dict carries
  `diff_pair_width`, `diff_pair_gap`, `diff_pair_via_gap`, plus `priority`
  (named classes use small ascending ints `0,1,2,…`; `Default` uses
  `2147483647`) and the full netclass shape (`clearance`, `track_width`,
  `via_diameter`, `via_drill`, colors, `bus_width`, `line_style`, `microvia_*`,
  `wire_width`, `name`). Named diff-pair classes here: `DDR4_BYTE0..3`,
  `DDR4_CMD`, `FPGA_HD`, `FPGA_HP`, `VMEPX`, `zse_50r`.
- **Net → netclass assignment** — `net_settings.netclass_patterns`: a list of
  `{"netclass": "<name>", "pattern": "<glob>"}` (key order `netclass` then
  `pattern`). `net_settings.netclass_assignments` is `null`. Multiple patterns
  may map to one class.
- **Length matching + diff-pair geometry (`.kicad_dru`)** — `(version 1)` header;
  length rules are
  `(rule "<name>" (constraint length (min Xmm) (max Ymm) (opt Zmm)) (condition "A.NetClass == '<class>' && A.fromTo('REFA-*','REFB-*')"))`;
  diff-pair rules use `(constraint diff_pair_gap (min..) (max..) (opt..))` +
  `(condition "A.inDiffPair('*')")`.

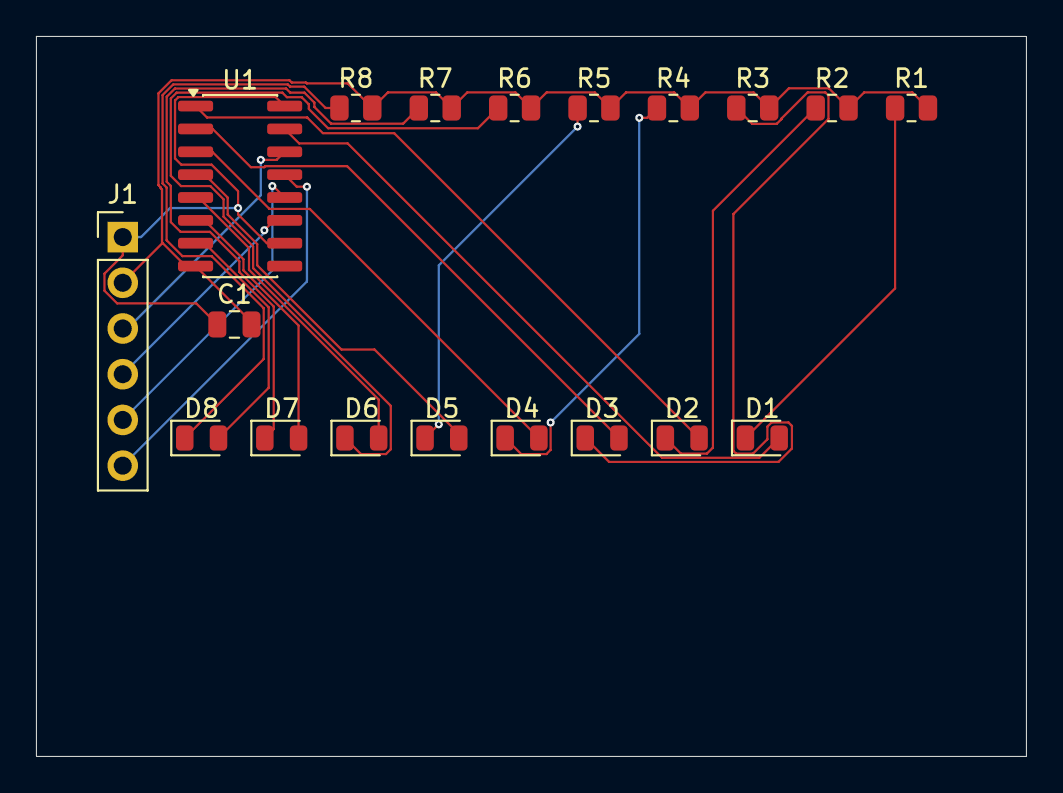
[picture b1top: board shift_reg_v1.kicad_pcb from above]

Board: 2 copper layers, 55.0 x 40.0 mm, 19 parts (0 on the bottom side), 22 nets.

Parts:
C1: C_0805_2012Metric
D1, D2, D3, D4, D5, D6, D7, D8: LED_0805_2012Metric
J1: PinHeader_1x06_P2.54mm_Vertical
R1, R2, R3, R4, R5, R6, R7, R8: R_0805_2012Metric
U1: SOIC-16_3.9x9.9mm_P1.27mm

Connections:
D1_K: D1.1, R1.1
D2_K: D2.1, R2.1
D3_K: D3.1, R3.1
D4_K: D4.1, R4.1
D5_K: D5.1, R5.1
D6_K: D6.1, R6.1
D7_K: D7.1, R7.1
D8_K: D8.1, R8.1
GND: C1.2, J1.2, R1.2, R2.2, R3.2, R4.2, R5.2, R6.2, R7.2, R8.2, U1.8
LATCH: J1.5, U1.12
QA: D1.2, U1.15
QB: D2.2, U1.1
QC: D3.2, U1.2
QD: D4.2, U1.3
QE: D5.2, U1.4
QF: D6.2, U1.5
QG: D7.2, U1.6
QH: D8.2, U1.7
SCK: J1.4, U1.11
SDI: J1.3, U1.14
VCC: C1.1, J1.1, U1.10, U1.16
nOE: J1.6, U1.13

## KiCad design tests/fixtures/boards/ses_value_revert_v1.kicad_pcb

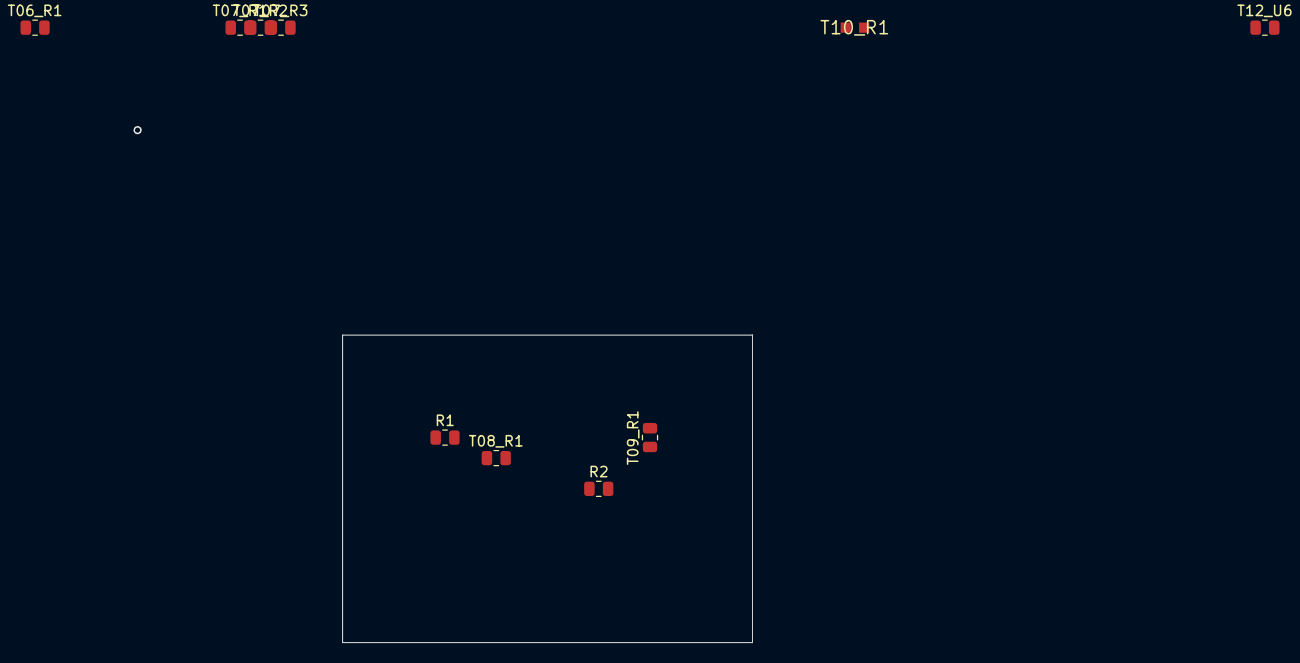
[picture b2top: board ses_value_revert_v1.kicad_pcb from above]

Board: 2 copper layers, 40.0 x 30.0 mm, 10 parts (0 on the bottom side), 2 nets.

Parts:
R1: Adafruit_PMSA003I; R_0805_2012Metric
R2: R_0805_2012Metric
T06_R1, T07_R1, T07_R2, T07_R3, T08_R1, T09_R1: R_0805_2012Metric
T10_R1: R_Test
T12_U6: Adafruit_PMSA003I; R_0805_2012Metric

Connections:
NETA: R1.1, R2.1
NETB: R1.2, R2.2

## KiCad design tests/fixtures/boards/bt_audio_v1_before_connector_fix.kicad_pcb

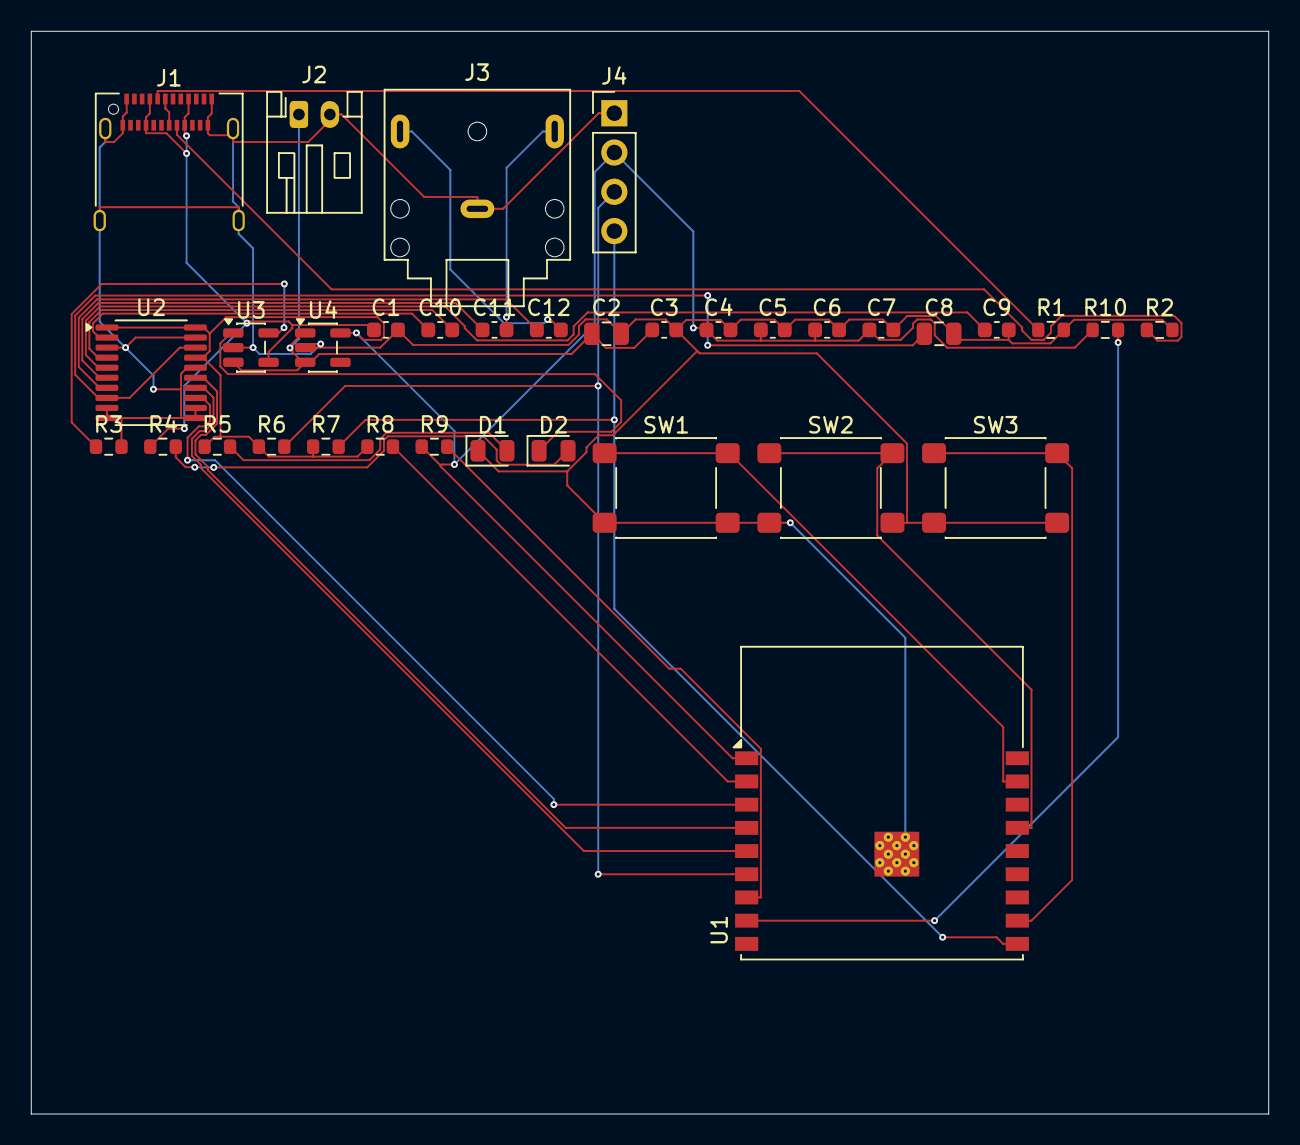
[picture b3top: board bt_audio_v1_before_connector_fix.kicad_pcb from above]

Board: 2 copper layers, 80.0 x 70.0 mm, 35 parts (0 on the bottom side), 31 nets.

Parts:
C1, C3, C4, C9, C10, C11, C12: 1uF; C_0603_1608Metric
C2, C8: 10uF; C_0805_2012Metric
C5, C6, C7: 0.1uF; C_0603_1608Metric
D1: PWR_GRN; LED_0805_2012Metric
D2: CHG_RED; LED_0805_2012Metric
J1: USB-C; USB_C_Receptacle_Amphenol_12401610E4-2A
J2: BAT; JST_PH_S2B-PH-K_1x02_P2.00mm_Horizontal
J3: TRS; Jack_3.5mm_CUI_SJ1-3523N_Horizontal
J4: OLED; PinHeader_1x04_P2.54mm_Vertical
R1, R2: 5k1; R_0603_1608Metric
R3: 2k; R_0603_1608Metric
R4, R5: 1k; R_0603_1608Metric
R6, R7: 4k7; R_0603_1608Metric
R8, R9, R10: 10k; R_0603_1608Metric
SW1: VOL_DN; SW_SPST_PTS645Sx43SMTR92
SW2: PLAY; SW_SPST_PTS645Sx43SMTR92
SW3: VOL_UP; SW_SPST_PTS645Sx43SMTR92
U1: ESP32-C3-WROOM-02
U2: PCM5102A; TSSOP-20_4.4x6.5mm_P0.65mm
U3: MCP73831-2-OT; SOT-23-5
U4: AP2112K-3.3; SOT-23-5

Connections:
+3V3: C4.1, C5.1, C6.1, C7.1, J4.2, R5.1, R6.1, R7.1, R8.1, R9.1, R10.1, U1.1, U2.1, U2.17, U2.20, U4.5
+BATT: C2.1, C3.1, J2.1, U3.3, U4.1, U4.3
AVDD_LDOO: C8.1, U2.8, U2.18
BTN_PLAY: SW2.1, U1.15
BTN_VOL_DN: SW1.1, U1.17
BTN_VOL_UP: SW3.1, U1.11
CAPM_FLY: C10.2, U2.4
CAPP_FLY: C10.1, U2.2
CC1: J1.A5, R1.1
CC2: J1.B5, R2.1
CHG_LED_A: D2.2, R4.2
EN_MCU: R8.2, U1.2
GND: C1.2, C2.2, C3.2, C4.2, C5.2, C6.2, C7.2, C8.2, C9.2, D1.1, J1.A1, J1.A12, J1.B1, J1.B12, J1.S1, J2.2, J3.S, J4.1, R1.2, R2.2, R3.2, SW1.2, SW2.2, SW3.2, U1.9, U1.19, U2.3, U2.9, U2.10, U2.11, U2.12, U2.16, U2.19, U3.2, U4.2
I2C_SCL: J4.4, R7.2, U1.10
I2C_SDA: J4.3, R6.2, U1.6
I2S_BCK: U1.3, U2.13
I2S_DIN: U1.5, U2.14
I2S_LRCK: U1.4, U2.15
OUTL_DAC: C11.1, U2.6
OUTR_DAC: C12.1, U2.7
OUT_LEFT: C11.2, J3.T
OUT_RIGHT: C12.2, J3.R
PROG: R3.1, U3.5
PWR_LED_A: D1.2, R5.2
STAT: D2.1, U3.1
STRAP_IO8: R9.2, U1.7
STRAP_IO9: R10.2, U1.8
USB_DM: J1.A7, J1.B7
USB_DP: J1.A6, J1.B6
VBUS: C1.1, J1.A4, J1.A9, J1.B4, J1.B9, R4.1, U3.4
VNEG: C9.1, U2.5

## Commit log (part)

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2026-02-15 Initial commit of KiCad MCP server
    Full implementation of Model Context Protocol server for KiCad EDA,
    including backends, tools, models, resources, examples, and tests.
2026-02-15 Add schematic pin positions, no-connects, junctions, and power symbols
    Implements 4 new tools (get_symbol_pin_positions, add_no_connect,
    add_power_symbol, add_junction) and enriches existing tools based on
    lessons from manual schematic rebuilds. add_component now supports
    rotation, mirror, footprint, and custom properties. read_schematic
    now returns no-connects, junctions, footprint, and is_power flag.
    Pin position parsing added to get_symbol_info with coordinate
2026-02-15 Add compare_schematic_pcb diagnostic tool for detecting sch/pcb mismatches
    Read-only tool that compares schematic symbols against PCB footprints and
    reports: components missing from PCB, components missing from schematic,
    footprint mismatches, and value mismatches. Power symbols (refs starting
    with '#' or is_power=True) are automatically excluded from comparison.
    P0 item #1 complete — all 5 P0 enhancements are now implemented.
2026-02-17 Add auto-routing tools for FreeRouting integration
    5 new MCP tools for automated PCB trace routing:
    - export_dsn: Export PCB to Specctra DSN format
    - import_ses: Import routed SES session back into PCB
    - run_freerouter: Execute FreeRouting auto-router
    - clean_board_for_routing: Remove keepouts and bad tracks
    - autoroute: Full pipeline orchestrating all steps
2026-02-19 feat: Implement extensive new backend capabilities and MCP tools
    This commit introduces a significant expansion of the KiCad MCP Server's
    functionality, primarily focusing on enhancing the capabilities of the
    file_backend and ipc_backend to support a wider range of read and write
    operations for both PCB board and schematic files.
    Key changes include:
    - **Expanded Backend Capabilities**:
2026-02-21 test: add integration test suite; fix suggest_footprints 50-cap bug
    - Add tests/integration/run_integration_tests.py: standalone script that
    exercises all 64 MCP tools against a real temp KiCad project.
    Result: 62 passed, 2 skipped (FreeRouting JAR), 0 failed.
    - Fix suggest_footprints() in FileLibraryOps: was calling
    search_footprints("") which returns only the first 50 footprints
    alphabetically (Audio_Module, Battery...). None matched R_* filters.
2026-02-21 test: add real MCP protocol integration test (64/64 tools pass)
    - Add examples/air_quality_sensor/test_tools.py: end-to-end integration
    test that launches the KiCad MCP server as a subprocess via stdio
    JSON-RPC (same transport as Claude Desktop) and exercises all 64 tools
    against a real air quality sensor project built from scratch
    - Fix file_backend: _ensure_lib_symbol_cached now accepts schematic_path
    and searches the project sym-lib-table for custom symbol libraries
2026-02-26 feat: add run.ps1 to auto-bootstrap and run in isolated venv
    Creates .venv on first run, installs kicad-mcp into it, then
    launches the server — keeping the global Python environment untouched.
    Subsequent runs skip setup and start immediately.
2026-02-27 chore: remove examples from tracking, add to .gitignore
    Examples are local test files and should not be versioned.
2026-03-02 docs: document response size limiting and truncation behaviour
    Add to Key Features and Troubleshooting sections explaining that
    read_schematic / read_board automatically cap large lists and emit
    *_total / *_truncated metadata, and suggest the focused per-list
    tools for large designs.
2026-03-10 docs: update README and LESSONS_LEARNED to reflect 78 tools and wearable_aqs example
    README:
    - Tool count 75 → 78; Project Management 11→13, PCB Board 13→14 section headers
    - Add plan_project, read_project_plan to Project Management listing
    - Add add_board_outline to PCB Board Operations listing
    - Correct set_board_design_rules description (targets .kicad_pro, not PCB setup block)
    - Add wearable_aqs to project structure tree and Examples section
2026-04-07 feat: Linux/macOS bridge install script + cross-platform docs
    - Add kicad_plugin/install_bridge.sh for Linux and macOS
    - Detects OS; resolves XDG paths on Linux, ~/Library/Preferences on macOS
    - Removes stale scripting/plugins copies (sys.modules conflict fix)
    - Installs to 3rdparty/plugins/kicad_mcp_bridge/__init__.py
    - Patches pcbnew.json action_plugins via python3 inline script
    - README: plugin backend now described as cross-platform (Windows/Linux/macOS)
2026-04-26 fix: make MCP server launch and integration tests cross-platform (Linux/macOS/Windows)
    - Replace Windows-only PowerShell command in .mcp.json with `python3 run.py`
    - Add run.py: a cross-platform venv bootstrapper that mirrors run.sh/run.ps1
    using only stdlib (os.execv on POSIX, subprocess on Windows)
    - Fix CLAUDE.md test command: Scripts/activate → bin/activate (Linux path)
    - Fix integration tests: replace three hardcoded C:/Program Files/KiCad paths
    with find_kicad_cli() and get_system_library_paths() so tests skip gracefully
2026-04-26 fix: resolve two non-blocking Linux issues from integration test run
    1. test_ipc_backend.py: add autouse _stub_kipy fixture that injects minimal
    kipy.proto.common.types stubs when kicad-python is not installed. Without
    this, the lazy DocumentType import inside get_active_project() raises
    ImportError which is swallowed by the existing try/except before the mock's
    get_open_documents() is ever called, causing open_documents_calls == 0 and
    breaking the Linux fallback assertions. Real kipy install is unaffected.
2026-04-29 fix: file backend read-only, kicad-cli .kicad_pro preservation, bridge SetDrill
    - file_backend: remove BOARD_MODIFY, SCHEMATIC_MODIFY, ERC, LIBRARY_MANAGE from
    capabilities — file backend is now strictly read-only (BOARD_READ, SCHEMATIC_READ,
    LIBRARY_SEARCH only); board/schematic writes require plugin or IPC backend
    - file_backend: revert copper_edge_clearance workaround (0.20 → 0.30); the file
    backend's DRC rules don't affect kicad-cli which reads .kicad_pro directly
    - cli_backend: preserve .kicad_pro before kicad-cli pcb drc and restore after;
2026-05-01 docs: split CLAUDE.md — add src/ and kicad_plugin/ dev guidelines
    src/CLAUDE.md: pytest requirement, codebase layout, two entry points,
    how to add a tool, footprint fixtures, what not to do.
    kicad_plugin/CLAUDE.md: bridge reinstall workflow, threading rules,
    how to add a handler, sys.modules installation hazard.
    Root CLAUDE.md title/content trim (remove dev sections, rename to
    Usage Guidelines) deferred — file locked by running Claude Code session.
2026-05-04 docs: update README for plugin-only architecture
    Remove all references to IPC backend, SWIG backend, composite backend,
    legacy run.ps1/run.sh scripts, and KICAD_MCP_BACKEND env var now that
    the legacy backend chain is deleted.
    - "Multiple Backend Support" → "Plugin Backend Architecture" routing table
    - Removed pip install kicad-mcp[ipc] optional dependency entry
    - Added KICAD_MCP_PLUGIN_PORT=9760, removed KICAD_MCP_BACKEND=auto
2026-05-07 fix: route pcb_pipeline auto_place through backend, not FileBoardOps
    pcb_pipeline Step 4 was bypassing the backend with a direct
    FileBoardOps().auto_place() call, so it never used the live pcbnew
    geometry path even when the bridge was active. Switches to
    backend.get_board_modify_ops().auto_place() — same convention used
    by the rest of the pipeline and by the recent clear_routes rework.
2026-05-07 fix: assign_net bridge handler must update all pads with the same number
    The bridge handler returned after the first matching pad, leaving the
    rest unassigned. Footprints like ESP32-C3-WROOM-02 render their thermal
    or exposed pad as multiple SMD rects sharing one logical pad number;
    only the first rect got the net, so DRC reported false-positive 'shorting'
    violations on the other rects.
    The file backend already handled this correctly (its docstring even
2026-05-17 fix(test): mock _load_kicad_mod in PlacementIntent sync tests
    The Linux CI runner has no KiCad footprint libraries, so place_component
    fell back to a stub footprint without silk geometry, which made
    identify_edge_facing_connectors find no mating face. The anchored_at_edge
    branch never fired and test_sync_anchors_connector_when_outline_present
    failed on every pytest job. Local Windows passed because the JST PH
    library was on disk.
2026-05-25 fix(cli): make 'install-bridge' an actual argparse subcommand
    The CLI was documented everywhere as 'kicad-mcp install-bridge
    [--kicad-version ...]', but the implementation had no subparser --
    'install-bridge' was treated as an unrecognized positional arg and
    argparse exited with code 2 before any bridge work ran. The 'prog'
    string claimed the subcommand existed; nothing wired it up.
    Discovered when M2 CI failed at the install-bridge step (run
2026-05-25 chore(ci): diagnose whether apt kicad has python scripting bindings
    bridge_startup.log is now confirmed absent everywhere on disk after
    sha 7ff2f70 -- meaning pcbnew never imports the module, regardless of
    which user plugin dir we install to. The new hypothesis is that
    Ubuntu's apt kicad meta-package does not include python3-pcbnew, so
    pcbnew runs as a C++-only GUI with no Python plugin loader at all.
    Adds diagnostics to confirm/refute:
2026-06-11 feat(drc): add validate_symbol_footprint_pairs tool (HLRP 6.2, WIP)
    Walks all sub-sheets, resolves each symbol Footprint field to a
    .kicad_mod, and compares pin numbers to pad numbers. Blocking:
    missing pins / unresolvable libs; warning: extra pads. Includes
    TestPkg fixture library + five fixture schematics. Also fixes
    read_schematic lib_id extraction (kicad-skip str() returns raw
    source text, breaking is_power detection).
2026-06-11 docs(integration): rerunning the suite needs a board-file reset, not just a pcbnew restart
    Saved placements persist in the scratch .kicad_pcb across sessions, so a
    second full run sees duplicate refs and file-content assertions match
    the stale footprint (observed: two T08_R1 after back-to-back runs).
2026-06-12 feat(schematic): close S3 schematic gaps (#6, #5, #4, #9)
    Issue numbers refer to MCP-KNOWN-ISSUES.md.
    #6 remove_wire: match wires in KiCad's native multi-line form, in either
    endpoint order, comparing coordinates numerically; no-match errors
    list the 3 nearest wires with distances.
    #5 read_schematic: when the kicad-skip path raises or yields zero labels
    while the file plainly contains label blocks, fall back to the sexp
2026-06-23 fix(coherence): don't clobber newer disk when board.Load() fails on reload (S5 live-found)
    Live verification of S5 #14C surfaced a clobber: the bridge correctly refuses a
    mutation with stale_board when disk is newer, but the self-heal reload defeated
    it. KiCad 9 embedded pcbnew fails board.Load() (reload_board returns
    loaded=False), yet the bridge still reset the coherence baseline — so the
    client's retry passed the coherence check and saved the stale in-memory board,
    reverting the external on-disk edit. Exactly the #8/#14 data-loss hazard.
2026-06-24 fix(bridge): get_components must return footprint lib_id (S6 live-found)
    Live-found during S6 #2 verification: sync_schematic_to_pcb(apply_footprint_changes=True)
    against a live board reported footprint_changes_applied:0 — the swap never fired.
    Root cause: the bridge's get_components returned reference/value/x/y/layer/rotation
    but NOT the footprint lib_id, so sync's mismatch check (pcb_comp.get("footprint",""))
    always saw "" and skipped the swap branch entirely. The whole #2 bridge-path swap
    was unreachable on the live read path.
2026-06-26 feat(s10): diff-pair rules (#6.4) + mypy-strict hot files (#6.9)
    §6.4 — set_board_design_rules gains differential_pairs + length_matching:
    - _upsert_netclass / _assign_nets_to_class write named diff-pair netclasses
    (diff_pair_width/gap/via_gap) + net assignment via netclass_patterns in
    .kicad_pro (idempotent, Default untouched).
    - _apply_length_matching writes length constraints to the sibling .kicad_dru
    (approved new write surface, REQ-LEN-003) with a balanced-paren rule upsert

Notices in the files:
README.md:
License:
MIT License - See LICENSE file for details
